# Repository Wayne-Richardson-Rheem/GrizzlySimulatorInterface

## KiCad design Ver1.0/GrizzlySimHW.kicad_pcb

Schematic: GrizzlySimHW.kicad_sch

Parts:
C2, C11, C16, C17, C19, C27, C30, C31, C33, C34, C35, C39, C40, C45, C49, C50, C51, C52, C53, C54, C55, C56, C57, C58, C59, C60, C61: 0.1uF; C_0805_2012Metric; LCSC Part# C49678
C20, C21, C22, C36, C37, C38: 47uF; C_0805_2012Metric; LCSC Part# C16780
C23, C24, C25, C26, C41, C42, C43, C44: 2.2uF; C_0805_2012Metric; LCSC Part# C23692980
C28, C46: 100uF; C_Elec_8x10.2; LCSC Part# C3352
C29, C47: 4.7nF; C_0805_2012Metric; LCSC Part# C1744
C32, C48: 47pF; C_0805_2012Metric; LCSC Part# C14857
C62, C63, C64, C65, C66, C67, C68, C69: 10nF; C_0805_2012Metric; LCSC Part# C1710
D21: S5J-E3; D_SMC; LCSC Part# C382934
D22, D34: B560C; D_SMA; LCSC Part# C139681
D23, D35: Red LED; LED_0805_2012Metric_Pad1.15x1.40mm_HandSolder; LCSC Part# C94868
D46: Green LED; LED_0805_2012Metric_Pad1.15x1.40mm_HandSolder; LCSC Part# C84260
GND2: Digital Out; ScrewTerminal_1x08_P2.54mm_Vertical
J1, J3, J10: Screw_Terminal_01x02; PinHeader_1x02_P2.54mm_Vertical
J5, J8, J9, J14, J15, J26, J31: GND; ScrewTerminal_1x04_P2.54mm_Vertical
J6: 0-10VDC Input; ScrewTerminal_1x08_P2.54mm_Vertical
J7: RJ12 - EcoNet; RJ12_Amphenol_54601-x06_Horizontal
J37: PH2-14-UA; ADAM_PH2-14-UA
L1, L2: 8.2uH (SWPA8040S8R2MT); L_Sunlord_SWPA8040S; LCSC Part# C84610
P1: RPi Header; Raspberry_Pi_Zero_Socketed_THT_FaceDown_MountingHoles
R3, R4, R5, R6, R17, R18, R19, R20, R27, R28, R29, R30, R37, R38, R43, R44, R58, R60, R62, R64, R78, R79, R80, R81, R96, R101, R102, R103, R104, R124, R125, R126, R127, R128, R145, R146, R147, R148, R149, R175, R177, R178, R179: 10k; R_0805_2012Metric; LCSC Part# C17414
R65, R68, R70, R73, R83, R84, R85, R87, R105, R106, R107, R108, R129, R130, R131, R132, R150, R151, R152, R155, R181, R182, R183, R185: 40k; R_0805_2012Metric; LCSC Part# C5266069
R69: 120; R_0805_2012Metric; LCSC Part# C17437
R76, R77, R153, R154, R156, R157, R162, R164, R165, R166, R170, R173, R174, R176, R180, R184, R186, R187: 4.7k; R_0805_2012Metric; LCSC Part# C17673
R91, R114: 442k; R_0805_2012Metric; LCSC Part# C17699
R92: 53.6k; R_0805_2012Metric; LCSC Part# C245350
R93, R116: 150; R_0805_2012Metric; LCSC Part# C17471
R94, R122: 90.9k; R_0805_2012Metric; LCSC Part# C294745
R95, R123: 243k; R_0805_2012Metric; LCSC Part# C17573
R100, R133: 16.9k; R_0805_2012Metric; LCSC Part# C17484
R115: 180k; R_0805_2012Metric; LCSC Part# C22356790
R139: 150; R_0805_2012Metric; LCSC Part# C17408
U2: SN74LVC1G34DCKR; SOT-353_SC-70-5
U5, U7, U10: SN74LVC1G34DCKR; SOT-353_SC-70-5; LCSC Part# C353880
U6: MCP3208; SOIC-16_3.9x9.9mm_P1.27mm; LCSC Part# C16939
U13: SP3485EN; SOIC-8_3.9x4.9mm_P1.27mm; LCSC Part# C8963
U14, U15, U16, U17, U21, U22, U23, U24, U28, U29, U30, U31, U37, U38, U39, U40, U45, U46, U47, U48, U54, U55, U56, U57: OPA192IDBVR; SOT95P280X145-5N; LCSC Part# C139648
U19, U20, U35, U36, U50, U51: MCP4728-E_UN; SOP50P490X110-10N; LCSC Part# C108207
U25, U32: TPS54560DDAR; Texas_R-PDSO-G8_EP2.95x4.9mm_Mask2.4x3.1mm_ThermalVias; LCSC Part# C31966
U26, U27, U33, U34, U41, U42, U43, U44, U52, U53, U58, U59, U60, U61: AD5245BRJZ100-RL7; RJ_8_ADI; LCSC Part# C649402
U49: TCA9548APWR; SOP65P640X120-24N; LCSC Part# C130026
W1: 3; ScrewTerminal_1x02_P2.54mm_Vertical
W2: 4; ScrewTerminal_1x02_P2.54mm_Vertical
W3: 5; ScrewTerminal_1x02_P2.54mm_Vertical
W4: 6; ScrewTerminal_1x02_P2.54mm_Vertical
W5: 7; ScrewTerminal_1x02_P2.54mm_Vertical
W6: 8; ScrewTerminal_1x02_P2.54mm_Vertical
W7: 9; ScrewTerminal_1x02_P2.54mm_Vertical
W8: 10; ScrewTerminal_1x02_P2.54mm_Vertical
W9: 11; ScrewTerminal_1x02_P2.54mm_Vertical
W10: 12; ScrewTerminal_1x02_P2.54mm_Vertical
W11: 13; ScrewTerminal_1x02_P2.54mm_Vertical
W12: 14; ScrewTerminal_1x02_P2.54mm_Vertical
W13: 15; ScrewTerminal_1x02_P2.54mm_Vertical
W14: 16; ScrewTerminal_1x02_P2.54mm_Vertical

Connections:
+3V3: C11.1, C16.1, C17.1, C30.1, C31.1, C33.1, C34.1, C39.1, C40.1, C49.1, C50.1, C51.1, C52.1, C53.1, C54.1, C55.1, C56.1, C57.1, C58.1, C59.1, C60.1, C61.1, J3.1, J3.2, J37.12, P1.1, P1.17, R76.2, R77.2, R139.1, R145.1, R153.2, R154.2, R156.2, R157.2, R162.2, R164.2, R165.2, R166.2, R170.2, R173.2, R174.2, R176.2, R180.2, R184.2, R186.2, R187.2, U5.5 (VCC), U13.8 (VCC), U19.1 (VDD), U20.1 (VDD), U26.2 (VDD), U27.2 (VDD), U27.6 (AD0), U33.2 (VDD), U34.2 (VDD), U34.6 (AD0), U35.1 (VDD), U36.1 (VDD), U41.2 (VDD), U42.2 (VDD), U42.6 (AD0), U43.2 (VDD), U44.2 (VDD), U44.6 (AD0), U49.24 (VCC), U50.1 (VDD), U51.1 (VDD), U52.2 (VDD), U53.2 (VDD), U53.6 (AD0), U58.2 (VDD), U59.2 (VDD), U59.6 (AD0), U60.2 (VDD), U61.2 (VDD), U61.6 (AD0)
+5V: C2.1, C20.1, C21.1, C22.1, J1.1, J1.2, J37.1, J37.13, L1.2, P1.2, P1.4, R92.2, R93.1, U2.5 (VCC), U6.15 (Vref), U6.16 (Vdd), U7.5 (VCC), U10.5 (VCC)
+15VDC: C36.1, C37.1, C38.1, L2.2, R115.2, R116.1, U14.5, U15.5, U16.5, U17.5, U21.5, U22.5, U23.5, U24.5, U28.5, U29.5, U30.5, U31.5, U37.5, U38.5, U39.5, U40.5, U45.5, U46.5, U47.5, U48.5, U54.5, U55.5, U56.5, U57.5
/3: U26.7 (B), W1.2
/4: U27.7 (B), W2.2
/5: U33.7 (B), W3.2
/6: U34.7 (B), W4.2
/7: U41.7 (B), W5.2
/8: U42.7 (B), W6.2
/9: U43.7 (B), W7.2
/10: U44.7 (B), W8.2
/11: U52.7 (B), W9.2
/12: U53.7 (B), W10.2
/13: U58.7 (B), W11.2
/14: U59.7 (B), W12.2
/15: U60.7 (B), W13.2
/16: U61.7 (B), W14.2
/34VDC: C23.1, C24.1, C25.1, C26.1, C27.1, C28.1, C41.1, C42.1, C43.1, C44.1, C45.1, C46.1, D21.1 (K), R91.2, R114.2, U25.2 (VIN), U32.2 (VIN)
/A/D Ch0: C69.1, R3.1, R5.2, U6.1 (CH0)
/A/D Ch0 INPUT: J6.1, R3.2
/A/D Ch1: C67.1, R17.2, R19.1, U6.2 (CH1)
/A/D Ch1 INPUT: J6.2, R17.1
/A/D Ch2: C65.1, R27.1, R29.1, U6.3 (CH2)
/A/D Ch2 INPUT: J6.3, R27.2
/A/D Ch3: C62.1, R37.1, R43.2, U6.4 (CH3)
/A/D Ch3 INPUT: J6.4, R37.2
/A/D Ch4: C68.1, R4.1, R6.2, U6.5 (CH4)
/A/D Ch4 INPUT: J6.5, R4.2
/A/D Ch5: C66.1, R18.1, R20.2, U6.6 (CH5)
/A/D Ch5 INPUT: J6.6, R18.2
/A/D Ch6: C64.1, R28.1, R30.1, U6.7 (CH6)
/A/D Ch6 INPUT: J6.7, R28.2
/A/D Ch7: C63.1, R38.1, R44.2, U6.8 (CH7)
/A/D Ch7 INPUT: J6.8, R38.2
/DAC0 A: U17.3, U20.6 (VOUTA)
/DAC0 B: U15.3, U20.7 (VOUTB)
/DAC0 C: U20.8 (VOUTC), U24.3
/DAC0 D: U20.9 (VOUTD), U22.3
/DAC0 Vo (0-10VDC) 1: J9.1, R73.2, U17.1
/DAC0 Vo (0-10VDC) 2: J9.2, R68.2, U15.1
/DAC0 Vo (0-10VDC) 3: J9.3, R87.2, U24.1
/DAC0 Vo (0-10VDC) 4: J9.4, R84.2, U22.1
/DAC1 A: U16.3, U19.6 (VOUTA)
/DAC1 B: U14.3, U19.7 (VOUTB)
/DAC1 C: U19.8 (VOUTC), U23.3
/DAC1 D: U19.9 (VOUTD), U21.3
/DAC1 Vo (0-10VDC) 1: J8.1, R70.2, U16.1
/DAC1 Vo (0-10VDC) 2: J8.2, R65.2, U14.1
/DAC1 Vo (0-10VDC) 3: J8.3, R85.2, U23.1
/DAC1 Vo (0-10VDC) 4: J8.4, R83.2, U21.1
/DAC2 A: U31.3, U36.6 (VOUTA)
/DAC2 B: U29.3, U36.7 (VOUTB)
/DAC2 C: U36.8 (VOUTC), U40.3
/DAC2 D: U36.9 (VOUTD), U38.3
/DAC2 Vo (0-10VDC) 1: J15.1, R108.2, U31.1
/DAC2 Vo (0-10VDC) 2: J15.2, R106.2, U29.1
/DAC2 Vo (0-10VDC) 3: J15.3, R132.2, U40.1
/DAC2 Vo (0-10VDC) 4: J15.4, R130.2, U38.1
/DAC3 A: U30.3, U35.6 (VOUTA)
/DAC3 B: U28.3, U35.7 (VOUTB)
/DAC3 C: U35.8 (VOUTC), U39.3
/DAC3 D: U35.9 (VOUTD), U37.3
/DAC3 Vo (0-10VDC) 1: J14.1, R107.2, U30.1
/DAC3 Vo (0-10VDC) 2: J14.2, R105.2, U28.1
/DAC3 Vo (0-10VDC) 3: J14.3, R131.2, U39.1
/DAC3 Vo (0-10VDC) 4: J14.4, R129.2, U37.1
/DAC4 A: U48.3, U51.6 (VOUTA)
/DAC4 B: U46.3, U51.7 (VOUTB)
/DAC4 C: U51.8 (VOUTC), U57.3
/DAC4 D: U51.9 (VOUTD), U55.3
/DAC4 Vo (0-10VDC) 1: J31.1, R155.2, U48.1
/DAC4 Vo (0-10VDC) 2: J31.2, R151.2, U46.1
/DAC4 Vo (0-10VDC) 3: J31.3, R185.2, U57.1
/DAC4 Vo (0-10VDC) 4: J31.4, R182.2, U55.1
/DAC5 A: U47.3, U50.6 (VOUTA)
/DAC5 B: U45.3, U50.7 (VOUTB)
/DAC5 C: U50.8 (VOUTC), U56.3
/DAC5 D: U50.9 (VOUTD), U54.3
/DAC5 Vo (0-10VDC) 1: J26.1, R152.2, U47.1
/DAC5 Vo (0-10VDC) 2: J26.2, R150.2, U45.1
/DAC5 Vo (0-10VDC) 3: J26.3, R183.2, U56.1
/DAC5 Vo (0-10VDC) 4: J26.4, R181.2, U54.1
/GPIO0 (ID_SD): GND2.4, P1.27
/GPIO1 (ID_SC): J37.4, P1.28
/GPIO2 (I2C1 SDA): J37.11, P1.3, R156.1, U49.23 (SDA)
/GPIO3 (I2C1 SCL): J37.9, P1.5, R153.1, U49.22 (SCL)
/GPIO4 (GPCLK0): GND2.1, P1.7
/GPIO5: P1.29, U20.4 (~LDAC)
/GPIO6: P1.31, U19.4 (~LDAC)
/GPIO7 (SPI0 CE1): J37.2, P1.26
/GPIO8 (SPI0 CE0): P1.24, U10.2 (A)
/GPIO9 (SPI0 MISO): P1.21, U5.4 (Y)
/GPIO10 (SPI0 MOSI): P1.19, U7.2 (A)
/GPIO11 (SPI0 SCLK): P1.23, U2.2 (A)
/GPIO12 (PWM0): P1.32, R145.2, U49.3 (~RESET)
/GPIO13 (PWM1): GND2.5, P1.33
/GPIO14 (UART Tx): P1.8, U13.4 (DI)
/GPIO15 (UART Rx): P1.10, U13.1 (RO)
/GPIO16: J37.6, P1.36
/GPIO17: P1.11, U35.4 (~LDAC)
/GPIO18 (PCM CLK): GND2.7, P1.12
/GPIO19 (PCM FS): GND2.6, P1.35, U13.3 (DE)
/GPIO20 (PCM DIN): P1.38, U50.4 (~LDAC)
/GPIO21 (PCM DOUT): J37.14, P1.40
/GPIO22: P1.15, U36.4 (~LDAC)
/GPIO23: GND2.2, P1.16
/GPIO24: GND2.3, P1.18
/GPIO27: P1.13, U51.4 (~LDAC)
/INTA*: J37.10, P1.37
/INTB*: J37.8, P1.22
/SC0: R76.1, U19.2 (SCL), U20.2 (SCL), U35.2 (SCL), U36.2 (SCL), U49.5 (SC0), U50.2 (SCL), U51.2 (SCL)
/SC1: R157.1, U26.4 (SCL), U27.4 (SCL), U49.7 (SC1)
/SC2: R164.1, U33.4 (SCL), U34.4 (SCL), U49.9 (SC2)
/SC3: R166.1, U41.4 (SCL), U42.4 (SCL), U49.11 (SC3)
/SC4: R173.1, U43.4 (SCL), U44.4 (SCL), U49.14 (SC4)
/SC5: R176.1, U49.16 (SC5), U52.4 (SCL), U53.4 (SCL)
/SC6: R184.1, U49.18 (SC6), U58.4 (SCL), U59.4 (SCL)
/SC7: R187.1, U49.20 (SC7), U60.4 (SCL), U61.4 (SCL)
/SD0: R77.1, U19.3 (SDA), U20.3 (SDA), U35.3 (SDA), U36.3 (SDA), U49.4 (SD0), U50.3 (SDA), U51.3 (SDA)
/SD1: R154.1, U26.5 (SDA), U27.5 (SDA), U49.6 (SD1)
/SD2: R162.1, U33.5 (SDA), U34.5 (SDA), U49.8 (SD2)
/SD3: R165.1, U41.5 (SDA), U42.5 (SDA), U49.10 (SD3)
/SD4: R170.1, U43.5 (SDA), U44.5 (SDA), U49.13 (SD4)
/SD5: R174.1, U49.15 (SD5), U52.5 (SDA), U53.5 (SDA)
/SD6: R180.1, U49.17 (SD6), U58.5 (SDA), U59.5 (SDA)
/SD7: R186.1, U49.19 (SD7), U60.5 (SDA), U61.5 (SDA)
/xlated_spi_clk: U2.4 (Y), U6.13 (CLK)
/xlated_spi_cs0: U6.10 (~CS/SHDN), U10.4 (Y)
/xlated_spi_miso: U5.2 (A), U6.12 (Dout)
/xlated_spi_mosi: U6.11 (Din), U7.4 (Y)
GND: C2.2, C11.2, C16.2, C17.2, C20.2, C21.2, C22.2, C23.2, C24.2, C25.2, C26.2, C27.2, C28.2, C29.1, C30.2, C31.2, C32.1, C33.2, C34.2, C36.2, C37.2, C38.2, C39.2, C40.2, C41.2, C42.2, C43.2, C44.2, C45.2, C46.2, C47.1, C48.1, C49.2, C50.2, C51.2, C52.2, C53.2, C54.2, C55.2, C56.2, C57.2, C58.2, C59.2, C60.2, C61.2, C62.2, C63.2, C64.2, C65.2, C66.2, C67.2, C68.2, C69.2, D22.2 (A), D23.1 (K), D34.2 (A), D35.1 (K), D46.1 (K), GND2.8, J5.1, J5.2, J5.3, J5.4, J10.2, J37.3, J37.5, J37.7, P1.6, P1.9, P1.14, P1.20, P1.25, P1.30, P1.34, P1.39, R5.1, R6.1, R19.2, R20.1, R29.2, R30.2, R43.1, R44.1, R58.1, R60.1, R62.1, R64.1, R78.1, R79.1, R80.1, R81.1, R94.2, R95.1, R96.2, R101.1, R102.1, R103.1, R104.1, R122.2, R123.1, R124.1, R125.1, R126.1, R127.2, R128.1, R146.1, R147.1, R148.1, R149.1, R175.1, R177.1, R178.1, R179.1, U2.3 (GND), U5.3 (GND), U6.9 (DGND), U6.14 (AGND), U7.3 (GND), U10.3 (GND), U13.2 (~RE), U13.5 (GND), U14.2, U15.2, U16.2, U17.2, U19.10 (VSS), U20.10 (VSS), U21.2, U22.2, U23.2, U24.2, U25.7 (GND), U25.9 (GND), U26.3 (GND), U26.6 (AD0), U27.3 (GND), U28.2, U29.2, U30.2, U31.2, U32.7 (GND), U32.9 (GND), U33.3 (GND), U33.6 (AD0), U34.3 (GND), U35.10 (VSS), U36.10 (VSS), U37.2, U38.2, U39.2, U40.2, U41.3 (GND), U41.6 (AD0), U42.3 (GND), U43.3 (GND), U43.6 (AD0), U44.3 (GND), U45.2, U46.2, U47.2, U48.2, U49.1 (A0), U49.2 (A1), U49.12 (GND), U49.21 (A2), U50.10 (VSS), U51.10 (VSS), U52.3 (GND), U52.6 (AD0), U53.3 (GND), U54.2, U55.2, U56.2, U57.2, U58.3 (GND), U58.6 (AD0), U59.3 (GND), U60.3 (GND), U60.6 (AD0), U61.3 (GND); also elsewhere on the board
unnamed: C29.2, R100.1
unnamed: C47.2, R133.1
unnamed: D21.2 (A), J10.1
unnamed: C19.2, D22.1 (K), L1.1, U25.8 (SW)
unnamed: D23.2 (A), R93.2
unnamed: C35.2, D34.1 (K), L2.1, U32.8 (SW)
unnamed: D35.2 (A), R116.2
unnamed: D46.2 (A), R139.2
unnamed: R58.2, R65.1, U14.4
unnamed: R60.2, R68.1, U15.4
unnamed: R62.2, R70.1, U16.4
unnamed: R64.2, R73.1, U17.4
unnamed: R78.2, R83.1, U21.4
unnamed: R79.2, R84.1, U22.4
unnamed: R80.2, R85.1, U23.4
unnamed: R81.2, R87.1, U24.4
unnamed: R101.2, R105.1, U28.4
unnamed: R102.2, R106.1, U29.4
unnamed: R103.2, R107.1, U30.4
unnamed: R104.2, R108.1, U31.4
unnamed: R124.2, R129.1, U37.4
unnamed: R125.2, R130.1, U38.4
unnamed: R126.2, R131.1, U39.4
unnamed: R128.2, R132.1, U40.4
unnamed: R146.2, R150.1, U45.4
unnamed: R147.2, R151.1, U46.4
unnamed: R148.2, R152.1, U47.4
unnamed: R149.2, R155.1, U48.4
unnamed: R175.2, R181.1, U54.4
unnamed: R177.2, R182.1, U55.4
unnamed: R178.2, R183.1, U56.4
unnamed: R179.2, R185.1, U57.4
unnamed: J7.4, R69.1, U13.6 (A)
unnamed: J7.3, R69.2, U13.7 (B)
unnamed: C19.1, U25.1 (BOOT)
unnamed: C32.2, R100.2, U25.6 (COMP)
unnamed: R91.1, R94.1, U25.3 (EN)
unnamed: R92.1, R96.1, U25.5 (FB)
unnamed: R95.2, U25.4 (RT/CLK)
unnamed: U26.1 (W), W1.1
unnamed: U27.1 (W), W2.1
unnamed: C35.1, U32.1 (BOOT)
unnamed: C48.2, R133.2, U32.6 (COMP)
unnamed: R114.1, R122.1, U32.3 (EN)
unnamed: R115.1, R127.1, U32.5 (FB)
unnamed: R123.2, U32.4 (RT/CLK)
unnamed: U33.1 (W), W3.1
unnamed: U34.1 (W), W4.1
unnamed: U41.1 (W), W5.1
unnamed: U42.1 (W), W6.1
unnamed: U43.1 (W), W7.1
unnamed: U44.1 (W), W8.1
unnamed: U52.1 (W), W9.1
unnamed: U53.1 (W), W10.1
unnamed: U58.1 (W), W11.1
unnamed: U59.1 (W), W12.1
unnamed: U60.1 (W), W13.1
unnamed: U61.1 (W), W14.1

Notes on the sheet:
DAC3
free
Source up to 500mA
DAC4
Is this circuit Voltage divider with 10kohm resistors correct for our application 0-10VDC to 0-5VDC
DAC2
I2C addressing for DAC0/DAC1 is stored in the EEPROM
Changed R56 value to 180k for feedback so that 15VDC can be achieved
DAC3
DAC1
DAC0
Rs-485/ RJ12 EcoNet Modbus will be communicated through USB on Raspberry Pi
Non-inverting Op-amp (Gain X2) used to step up voltage from 0-5vdc to 0-10vdc. Motors are 4-20ma
DAC5
24VAC to 5VDC Power Circuit
.1uf decoupling capacitors? Adafruit used 10uf
INTB
i2c Mux Reset
INTA
Grizzly Simulator I/F Board
20pA
24VAC to 15VDC Power Circuit
Grizzly/Nanook (2029 IVEC) Simulator Interface Board
Address 000
DAC5
DAC2
Av = R1/R2 + 1
Vout = (R37/R38)Vfb + Vfb Vfb = 0.8
GPIO MUX Reset
1400 uA
*GPIO MUX Reset
Board Stacker Connector
Rev 1.0
I2C Mux
I2C expander and Digi Pot circuit
24VAC Input

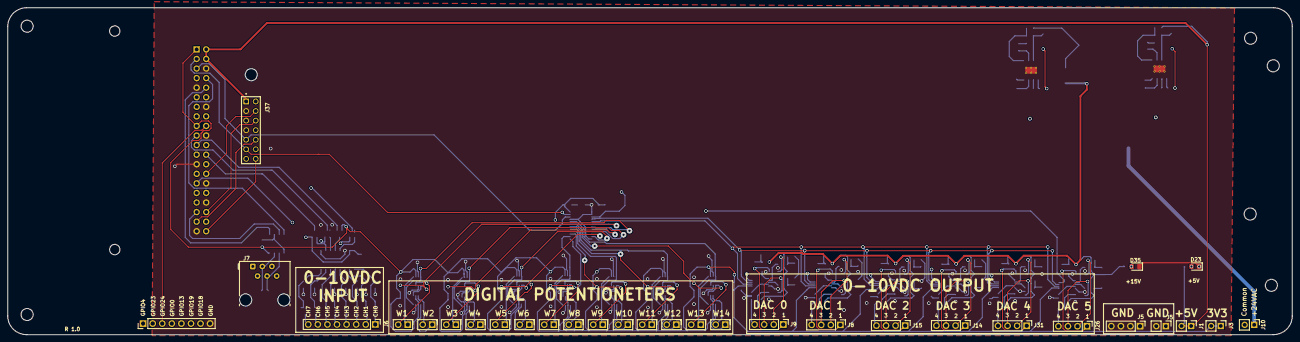
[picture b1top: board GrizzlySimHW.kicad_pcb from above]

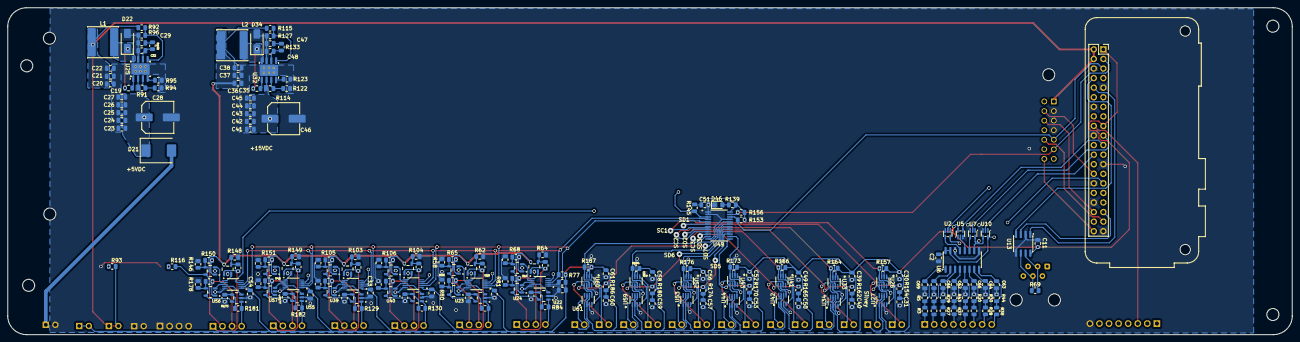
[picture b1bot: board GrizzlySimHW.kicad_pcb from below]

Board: 4 copper layers, 340.9 x 86.8 mm, 245 parts (214 on the bottom side), 189 nets.

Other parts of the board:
J5#2: Screw_Terminal_01x02; PinHeader_1x02_P2.54mm_Vertical

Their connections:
GND: J5#2.1, J5#2.2; also elsewhere on the board

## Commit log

2026-02-16 Created Versioning Directory Structure
    Added Ver1.0 Directory
2026-02-23 Updated Translator Part
    Changed the part number and LSCS Part number on the schematic and updated the BOM
